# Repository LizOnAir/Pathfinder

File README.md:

# Pathfinder
I want to learn more on programming instead of just doing PCB design and soldering, so is started with this project to explore what can I do with buttons and LEDs.

## Feature
A neatly designed PCB, with 3 buttons and 3 LEDs.

## PCB
Schematic

Layout

## Firmware
I added some secret function to the board.

## BOM

Here should be [everything](https://docs.google.com/spreadsheets/d/1EyjIwq-JwZ3a3lyBV-CAjp1h-FCLzlr-dAyOyNG1r50/edit?gid=0#gid=0) you need:

- 1x RP2040
- 1x PCB
- 3x LEDs
- 1x 470 resistor

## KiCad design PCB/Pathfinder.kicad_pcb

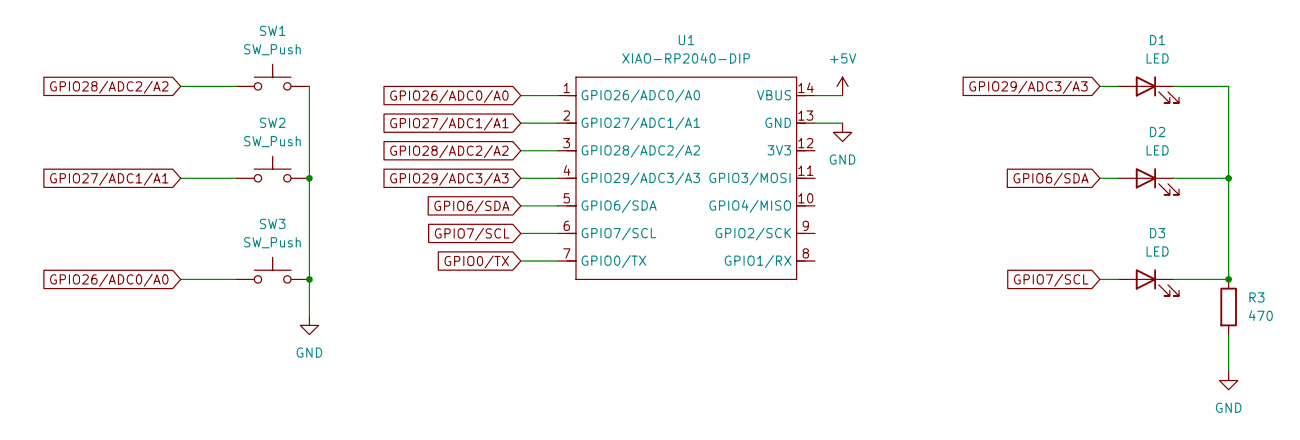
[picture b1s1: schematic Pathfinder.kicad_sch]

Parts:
D1, D2, D3: LED; LED_D5.0mm
R3: 470; R_Axial_DIN0207_L6.3mm_D2.5mm_P7.62mm_Horizontal
SW1, SW2, SW3: SW_Push; MX CHERRY SWITCH
U1: XIAO-RP2040-DIP

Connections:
+5V: U1.14 (VBUS)
GND: R3.2, SW1.2, SW2.2, SW3.2, U1.13 (GND)
GPIO0/TX: U1.7 (GPIO0/TX)
GPIO6/SDA: D2.2 (A), U1.5 (GPIO6/SDA)
GPIO7/SCL: D3.2 (A), U1.6 (GPIO7/SCL)
GPIO26/ADC0/A0: SW3.1, U1.1 (GPIO26/ADC0/A0)
GPIO27/ADC1/A1: SW2.1, U1.2 (GPIO27/ADC1/A1)
GPIO28/ADC2/A2: SW1.1, U1.3 (GPIO28/ADC2/A2)
GPIO29/ADC3/A3: D1.2 (A), U1.4 (GPIO29/ADC3/A3)
unnamed: D1.1 (K), D2.1 (K), D3.1 (K), R3.1

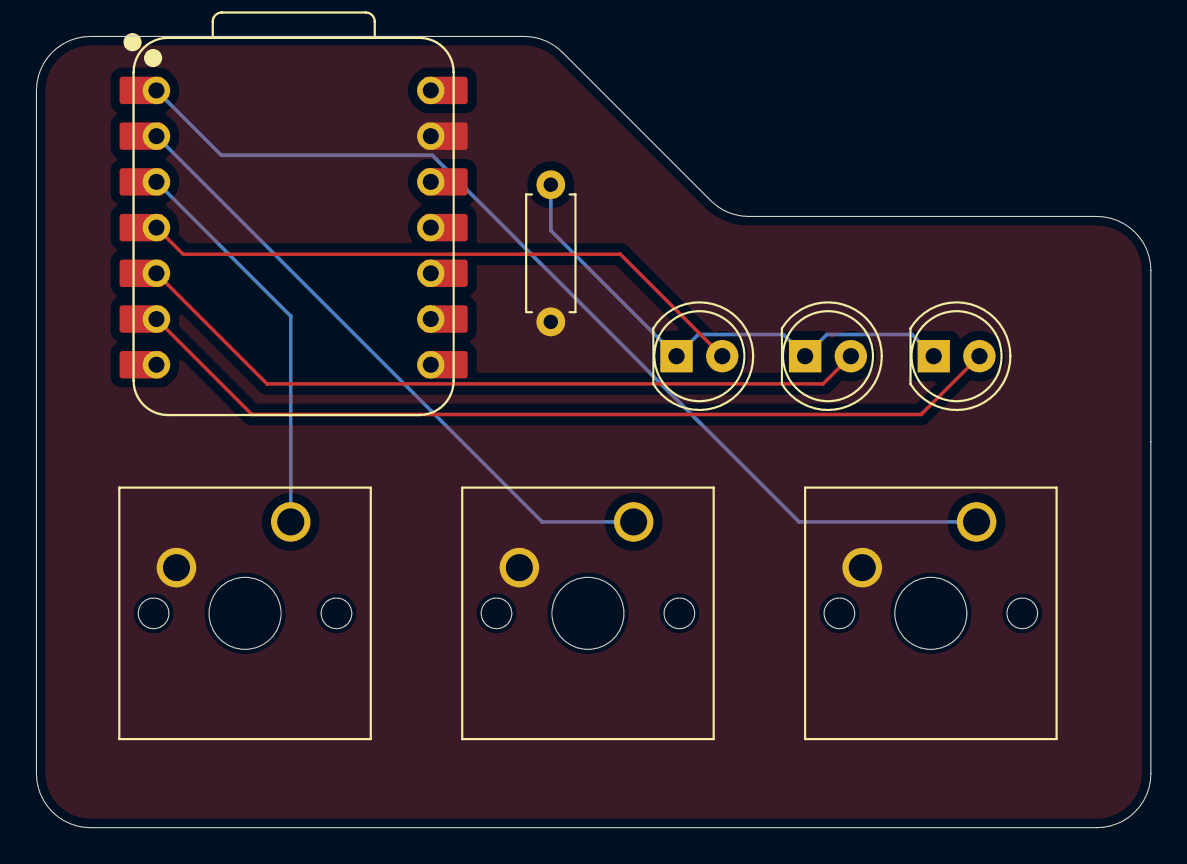
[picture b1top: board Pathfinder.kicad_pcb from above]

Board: 2 copper layers, 61.9 x 44.0 mm, 8 parts (0 on the bottom side), 8 nets.

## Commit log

2026-04-20 Rename Pathfinder.kicad_pro to PCB/Pathfinder.kicad_pro
2026-04-20 Fix BOM link in README
    Updated the BOM section with a corrected link.
2026-04-20 Rename Pathfinder.ino to Firmware/Pathfinder.ino
